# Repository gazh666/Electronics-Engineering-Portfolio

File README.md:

# Electronics Engineering Portfolio

**Power Electronics | Battery Management | Semiconductor Applications | PCB Design | Engineering Validation**

三个独立、可复现的电子工程项目：电池管理（BatteryLab）、电源电路仿真（PowerLab）、
自动化测试与工程验证（TestLab）。全部基于真实运行的 SPICE 求解、自动化测试与 KiCad EDA 检查，
不使用伪造数据、不把仿真写成实测、不隐藏失败结论。

> 本仓库为**个人工程研究原型**，未进行制板、焊接、上电或真实仪器/电池实验。
> 明确不含 **Production Ready / Hardware Validated** 表述。工程局限见
> [known_limitations.md](known_limitations.md)。

## 三个项目

- **BatteryLab — 电池管理系统**
  模拟前端采集、AFE 误差预算、MOSFET 保护、被动均衡、CC-CV 充电、SOC 估计，
  以及两套**真实可编辑的 KiCad 原理图 + 两块四层 PCB**。

- **PowerLab — 电源电路仿真**
  Buck 拓扑、功率器件非理想建模、效率与损耗分析、Pareto 多目标优化、PI 控制、软启动。

- **TestLab — 自动化测试与验证**
  SCPI 虚拟仪器、自动化测试、参数扫描、故障注入、工程验证与可靠性统计。

## BatteryLab 最终量化成果

每项均标注结果性质：`仿真` / `解析计算` / `公开数据分析` / `EDA 设计` / `软件测试`。

| 成果 | 数值 | 性质 | 证据 |
|---|---|---|---|
| 最坏情况电压采样误差预算 | 30.887 → 3.837 mV | 仿真 | `portfolio/BatteryLab_resume_metrics_v3.csv` |
| 最坏情况电流采样误差预算 | 37.736 → 6.666 mA | 仿真 | 同上 |
| 被动均衡单体压差 | 130 → 10.47 mV | 仿真 | 同上（B01） |
| 独立 MOSFET 保护 故障→电流抑制 | 0.871 µs | 仿真（SPICE 原始波形） | `BatteryLab/portfolio/BatteryLab_MOSFET保护真实性复验.md` |
| 联合系统保护 故障→电流抑制 | 119.8 µs（**RISK**） | 仿真 | `BatteryLab/portfolio/BatteryLab_研发岗成果证据卡_v3.md` |
| CC-CV 功率级效率 | 98.01 % | 仿真 | `BatteryLab/portfolio/BatteryLab_CC_CV控制优化前后对照.md` |
| CC 稳态误差 / CV 稳态误差 / CC→CV 过冲 | 1.09 mA / 13.50 mV / 2.07 mV | 仿真 | `BatteryLab/portfolio/BatteryLab_CC_CV控制优化前后对照.md` |
| SOC 估计 RMSE | 1.8247 个百分点 | 公开数据分析（CALCE 重放） | `BatteryLab/portfolio/BatteryLab_研发岗成果证据卡.md`（E01） |
| 可编辑原理图 | 2 套（BMS / 充电器） | EDA 设计 | `hardware/eda/*V2/` |
| 四层 PCB | 2 块，100.1 × 72.1 mm | EDA 设计 | `hardware/eda/*V2/release/routing_metrics.json` |
| 走线 / 过孔总数 | 620 段 / 96 个 | EDA 设计 | 两块板合计（304+316 / 46+50） |
| PCB 未连接项 | 65 / 51 → 0 / 0 | EDA 检查 | `release/unconnected_nets.csv` |
| DRC 错误 | 4 / 0 → 0 / 0 | EDA 检查 | `release/drc.json` |
| PCB 面积缩小 | 约 42 %（102×122 → 100.1×72.1 mm） | 解析计算 | [FINAL_DATA_AUDIT.md](docs/FINAL_DATA_AUDIT.md) |
| 软件回归测试 | 594 passed | 软件测试 | `BatteryLab/portfolio/BatteryLab_工程指标真实性核查报告_v3.md` |

> 以上均为仿真、解析计算、公开数据分析、EDA 设计或软件测试结果，
> **不是实际商业 BMS 板卡的硬件测量值**。

## PCB 真实预览（KiCad 导出 SVG）

以下为 `kicad-cli` 从实际 `.kicad_pcb` 导出的顶层/底层 SVG，不是渲染图或效果图。

**BMS V2（4 层，100.1 × 72.1 mm，304 段 / 46 过孔，0 未连接）**

**Charger V2（4 层，100.1 × 72.1 mm，316 段 / 50 过孔，0 未连接）**

**3D / STEP 查看说明**：本仓库**不提供伪造的 3D 渲染图**。如需 3D 视图，请下载
[BMS STEP](BatteryLab/hardware/eda/BatteryLab_BMS_V2/release/board.step) 或
[Charger STEP](BatteryLab/hardware/eda/BatteryLab_Charger_V2/release/board.step)，
用 KiCad PCB Editor、FreeCAD 或任意 STEP 查看器打开。

## 工程证据索引

- 完整证据索引：[docs/EVIDENCE_INDEX.md](docs/EVIDENCE_INDEX.md)
- 最终数据核查：[docs/FINAL_DATA_AUDIT.md](docs/FINAL_DATA_AUDIT.md)
- 前后工程对照：[BatteryLab/portfolio/BatteryLab_PCB工程设计前后对照.md](BatteryLab/portfolio/BatteryLab_PCB工程设计前后对照.md)
- ERC 告警分类：[BatteryLab/hardware/eda/review/schematic_warning_review.csv](BatteryLab/hardware/eda/review/schematic_warning_review.csv)
- 布线规划与叠层：[BatteryLab/hardware/eda/review/routing_plan.md](BatteryLab/hardware/eda/review/routing_plan.md)
- 性能优化前后对照：[BatteryLab/portfolio/BatteryLab_工程性能优化前后对照_v2.md](BatteryLab/portfolio/BatteryLab_工程性能优化前后对照_v2.md)
- 原理图 PDF：[BMS](BatteryLab/hardware/eda/BatteryLab_BMS_V2/release/schematic.pdf) /
  [Charger](BatteryLab/hardware/eda/BatteryLab_Charger_V2/release/schematic.pdf)

> 说明：原始运行输出（`results/`、pytest 日志）体积较大且含本机路径，**不随仓库分发**；
> 仓库内证据为汇总 CSV、验证文档与 EDA 发布文件，原始输出可按复现步骤在本地重新生成。

## 项目索引

| 项目 | 方向 | 关键技术 | 可复现证据 |
|---|---|---|---|
| [TestLab](TestLab/README.md) | 自动化测试 / 虚拟仪器 | PyVISA-sim、SCPI、行为模型 DUT、故障注入、可靠性、报告 | 557 passed、覆盖率 84%、发布验收 7/7 |
| [PowerLab](PowerLab/README.md) | 电源电路仿真 | PySpice 1.5 + ngspice 34、Buck 开环瞬态、CCM/DCM、理论对照 | ngspice 真实求解、11 项基础分析回归 |
| [BatteryLab](BatteryLab/README.md) | 电池采样 / 保护 / 充电 / EDA | 电池模型、AFE 误差预算、保护 SPICE、充电闭环、KiCad 4 层 PCB | 594 passed、ERC/DRC 0 错误、0 未连接 |

## 目录说明

```
Electronics-Engineering-Portfolio/
├── TestLab/                      # PyVISA-sim 自动化测试平台
├── PowerLab/                     # PySpice + ngspice 电源仿真
├── BatteryLab/                   # 电池软件链 + KiCad 硬件设计
│   ├── hardware/eda/
│   │   ├── BatteryLab_BMS_V1/    # 未布线工程草案（保留）
│   │   ├── BatteryLab_BMS_V2/    # 完成布线的工程研究版本
│   │   ├── BatteryLab_Charger_V1/
│   │   ├── BatteryLab_Charger_V2/
│   │   ├── requirements/         # 引脚映射、网络规则、接口定义
│   │   └── review/               # ERC 告警分类、QFN 审核、叠层、线宽计算
│   └── portfolio/                # 验收报告、前后对照、简历 v3/v4
├── docs/                         # 证据索引、复现步骤、许可与上传清单
└── known_limitations.md          # 已知工程局限（必读）
```

## 重要声明

1. **数据性质**：全部为 `spice_simulation` / `pyvisa-sim SCPI` / `behavioral_model` / EDA 检查结果，
   不是实验室实测。
2. **失败与风险照实保留**：保护联合工况 119.8 µs（RISK）、环路带宽分离 1.86×（FAIL）、
   负载阶跃超 300 mV 限值（FAIL/过载研究）、低 SOC 误差未达标（LIMITED）。
3. **EDA 边界**：PCB 已完成布线、DRC 0 错误 0 未连接，但热、EMI、阻抗、平面完整性、
   开关节点寄生参数均未验证，不得作为投产或实际电池接线依据。详见 [known_limitations.md](known_limitations.md)。
4. **许可证**：本人原创及 AI 辅助开发的代码采用 MIT；第三方代码、数据、SPICE 模型、封装及工具
   保留各自原始许可证，详见 [THIRD_PARTY_NOTICES.md](THIRD_PARTY_NOTICES.md)。
5. **AI 辅助**：代码整理与文档撰写使用了 AI 辅助；所有数值由仓库内脚本在本机计算，并保留原始输出。
6. **隐私**：仓库不包含密钥、令牌、账号、邮箱或个人绝对路径（上传前已做敏感信息扫描）。

## 复现

```powershell
# TestLab
conda create -n kaifa python=3.11 pip -y
conda run -n kaifa python -m pip install -r TestLab/requirements.txt -r TestLab/requirements-dev.txt
conda run -n kaifa python -m pytest TestLab/tests -q

# PowerLab（需要 ngspice DLL）
conda create -n kaifa_power python=3.11 pip -y
conda run -n kaifa_power python -m pip install -r PowerLab/requirements.txt
conda run -n kaifa_power pyspice-post-installation --install-ngspice-dll
conda run -n kaifa_power python -m pytest PowerLab/tests -q

# BatteryLab
conda create -n kaifa_battery python=3.11 pip -y
conda run -n kaifa_battery python -m pip install -r BatteryLab/requirements.txt
conda run -n kaifa_battery python -m pytest BatteryLab/tests -q
```

KiCad 部分需要 KiCad 10 与 `kicad-cli`，见 [BatteryLab/hardware/eda/review/tool_verification.md](BatteryLab/hardware/eda/review/tool_verification.md)。
完整复现步骤见 [docs/REPRODUCIBILITY.md](docs/REPRODUCIBILITY.md)。

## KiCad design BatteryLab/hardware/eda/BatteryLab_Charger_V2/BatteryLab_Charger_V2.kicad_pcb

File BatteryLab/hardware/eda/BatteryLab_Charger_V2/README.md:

# BatteryLab_Charger_V1 状态

**BLOCKED_NO_KICAD_GUI**：本机未安装 KiCad，本目录没有 KiCad 工程文件。
本阶段只完成了充电器**原理图级设计计算**，PCB 尚未开始。

已完成的输入：

- `../requirements/charger_design.yaml`：18 V→12.15 V/1 A、600 kHz、VFB=2.1 V
- `../requirements/charger_pin_mapping.csv`：25 行（24 引脚 + PAD）
- `../requirements/critical_net_rules.csv`：功率与采样网络规则
- `../component_selection/inductor_comparison.csv`：SRN6045-220M 选型
- `docs/84_bq24610_charger_design.md`：全部计算与依据

安装 KiCad 后的操作：

1. 新建工程并按引脚映射绘制原理图；
2. ERC 通过后再进入 PCB；
3. 已知待复核项：LC 谐振标称 11.07 kHz（低于 12–17 kHz）、30 V FET 对 32 V ACOV 的余量。

详见 `docs/78_kicad_environment.md` 与 `docs/90_stage8_final_validation.md`。

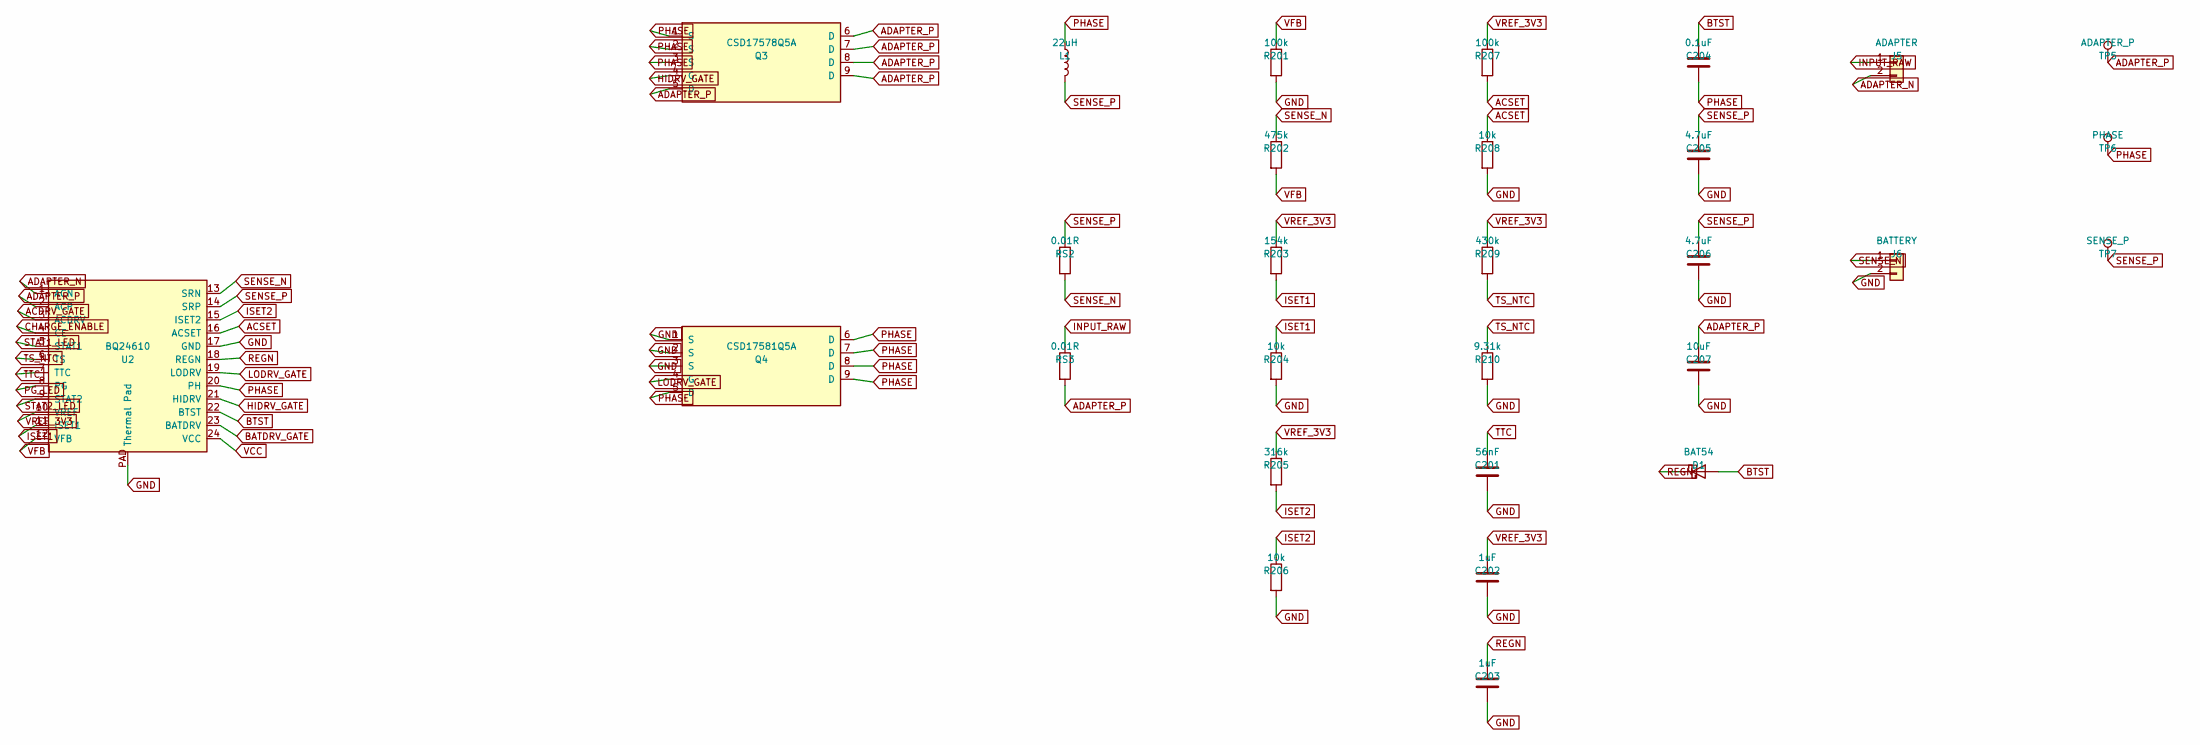
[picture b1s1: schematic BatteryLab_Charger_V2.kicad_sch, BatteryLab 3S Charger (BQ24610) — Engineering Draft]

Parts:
C201: 56nF; C_0603_1608Metric
C202, C203: 1uF; C_0603_1608Metric
C204: 0.1uF; C_0402_1005Metric
C205, C206: 4.7uF; C_1206_3216Metric
C207: 10uF; C_1206_3216Metric
D1: BAT54; D_SOD-323
J5: ADAPTER; PinHeader_1x02_P2.54mm_Vertical
J6: BATTERY; PinHeader_1x02_P2.54mm_Vertical
L1: 22uH; L_Bourns_SRN6045TA
Q3: CSD17578Q5A; Texas_S-PVSON-N8
Q4: CSD17581Q5A; Texas_S-PVSON-N8
R201, R207: 100k; R_0603_1608Metric
R202: 475k; R_0603_1608Metric
R203: 154k; R_0603_1608Metric
R204, R206, R208: 10k; R_0603_1608Metric
R205: 316k; R_0603_1608Metric
R209: 430k; R_0603_1608Metric
R210: 9.31k; R_0603_1608Metric
RS2, RS3: 0.01R; R_2010_5025Metric
TP5: ADAPTER_P; TestPoint_Pad_1.5x1.5mm
TP6: PHASE; TestPoint_Pad_1.5x1.5mm
TP7: SENSE_P; TestPoint_Pad_1.5x1.5mm
U2: BQ24610; Texas_RGE0024H_VQFN-24-1EP_4x4mm_P0.5mm_EP2.7x2.7mm

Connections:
ACDRV_GATE: U2.3 (ACDRV)
ACSET: R207.2, R208.1, U2.16 (ACSET)
ADAPTER_N: J5.2, U2.1 (ACN)
ADAPTER_P: C207.1, Q3.5 (D), Q3.6 (D), Q3.7 (D), Q3.8 (D), Q3.9 (D), RS3.2, TP5.1, U2.2 (ACP)
BATDRV_GATE: U2.23 (BATDRV)
BTST: C204.1, D1.2 (A), U2.22 (BTST)
CHARGE_ENABLE: U2.4 (CE)
GND: C201.2, C202.2, C203.2, C205.2, C206.2, C207.2, J6.2, Q4.1 (S), Q4.2 (S), Q4.3 (S), R201.2, R204.2, R206.2, R208.2, R210.2, U2.17 (GND), U2.PAD (Thermal Pad)
HIDRV_GATE: Q3.4 (G), U2.21 (HIDRV)
INPUT_RAW: J5.1, RS3.1
ISET1: R203.2, R204.1, U2.11 (ISET1)
ISET2: R205.2, R206.1, U2.15 (ISET2)
LODRV_GATE: Q4.4 (G), U2.19 (LODRV)
PG_LED: U2.8 (PG)
PHASE: C204.2, L1.1, Q3.1 (S), Q3.2 (S), Q3.3 (S), Q4.5 (D), Q4.6 (D), Q4.7 (D), Q4.8 (D), Q4.9 (D), TP6.1, U2.20 (PH)
REGN: C203.1, D1.1 (K), U2.18 (REGN)
SENSE_N: J6.1, R202.1, RS2.2, U2.13 (SRN)
SENSE_P: C205.1, C206.1, L1.2, RS2.1, TP7.1, U2.14 (SRP)
STAT1_LED: U2.5 (STAT1)
STAT2_LED: U2.9 (STAT2)
TS_NTC: R209.2, R210.1, U2.6 (TS)
TTC: C201.1, U2.7 (TTC)
VCC: U2.24 (VCC)
VFB: R201.1, R202.2, U2.12 (VFB)
VREF_3V3: C202.1, R203.1, R205.1, R207.1, R209.1, U2.10 (VREF)

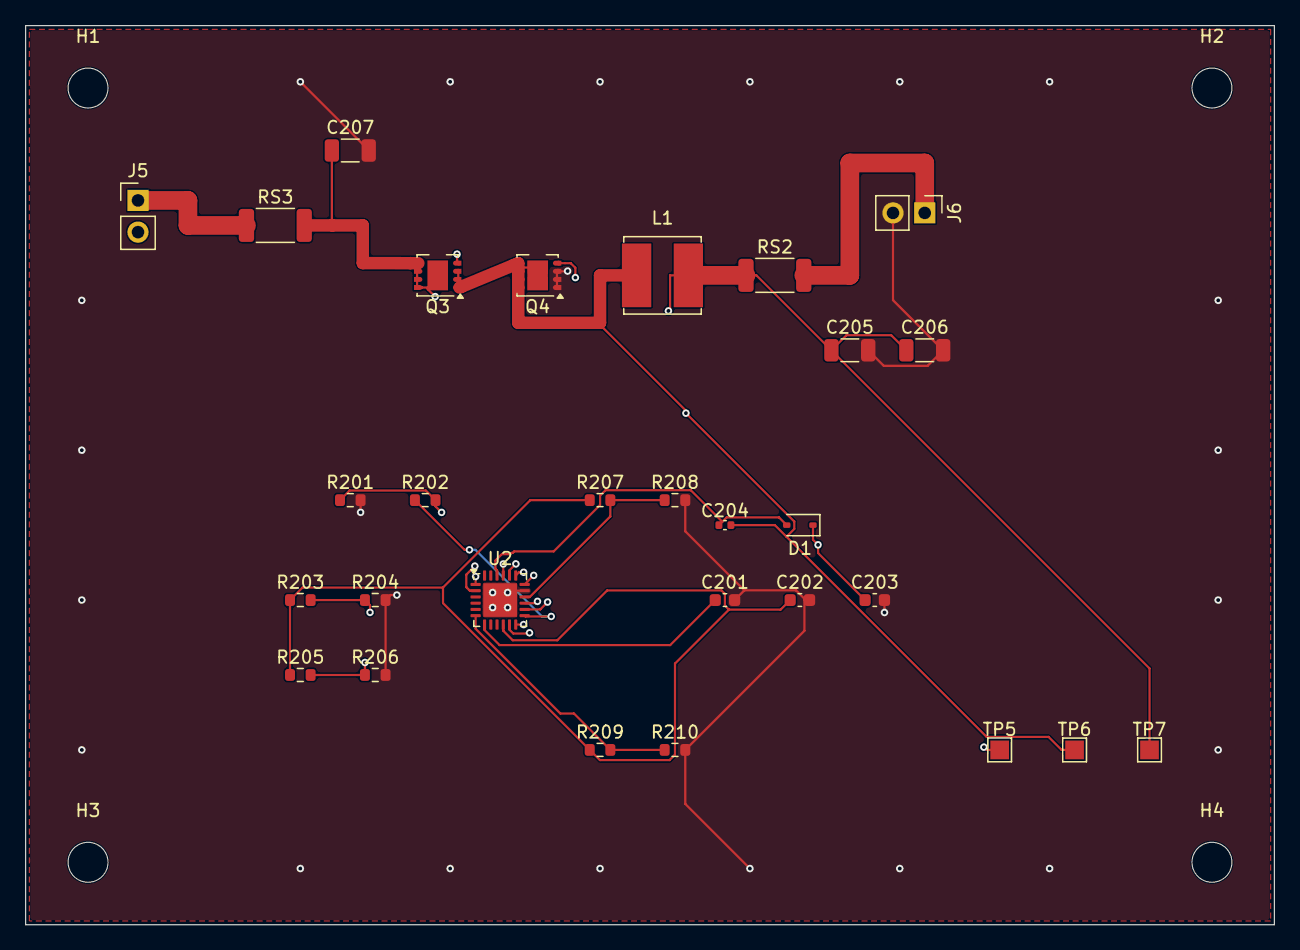
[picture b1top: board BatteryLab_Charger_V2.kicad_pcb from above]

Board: 4 copper layers, 100.0 x 72.0 mm, 33 parts (0 on the bottom side), 18 nets.

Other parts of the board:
H1, H2, H3, H4: MountingHole_3.2mm_M3

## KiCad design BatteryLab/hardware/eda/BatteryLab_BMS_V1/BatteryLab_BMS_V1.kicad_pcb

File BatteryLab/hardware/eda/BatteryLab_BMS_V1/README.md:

# BatteryLab_BMS_V1 状态

**BLOCKED_NO_KICAD_GUI**：本机未安装 KiCad，本目录没有 `.kicad_pro` /
`.kicad_sch` / `.kicad_pcb`。请不要把本目录当作已完成工程。

已完成的输入（可直接用于绘制原理图）：

- `../requirements/bms_design.yaml`：设计目标与 AFE 配置
- `../requirements/bms_pin_mapping.csv`：33 行（32 引脚 + PAD），逐行标注数据手册页码
- `../requirements/critical_net_rules.csv`：关键网络宽度/间距/层
- `../requirements/interface_definition.csv`：J1–J4、TP1–TP4
- `../../component_selection/`：器件与封装核查

安装 KiCad 后的操作：

1. 新建工程 `BatteryLab_BMS_V1.kicad_pro`；
2. 按引脚映射表放置符号并连线，封装按 `footprint_verification.csv` 核对；
3. 运行 `kicad-cli sch erc --format json ...`；
4. 布局布线后运行 `kicad-cli pcb drc --format json ...`；
5. 回到仓库根目录运行 `python -m scripts.audit_schematic` 与 `audit_pcb`。

详见 `docs/78_kicad_environment.md` 与 `docs/90_stage8_final_validation.md`。

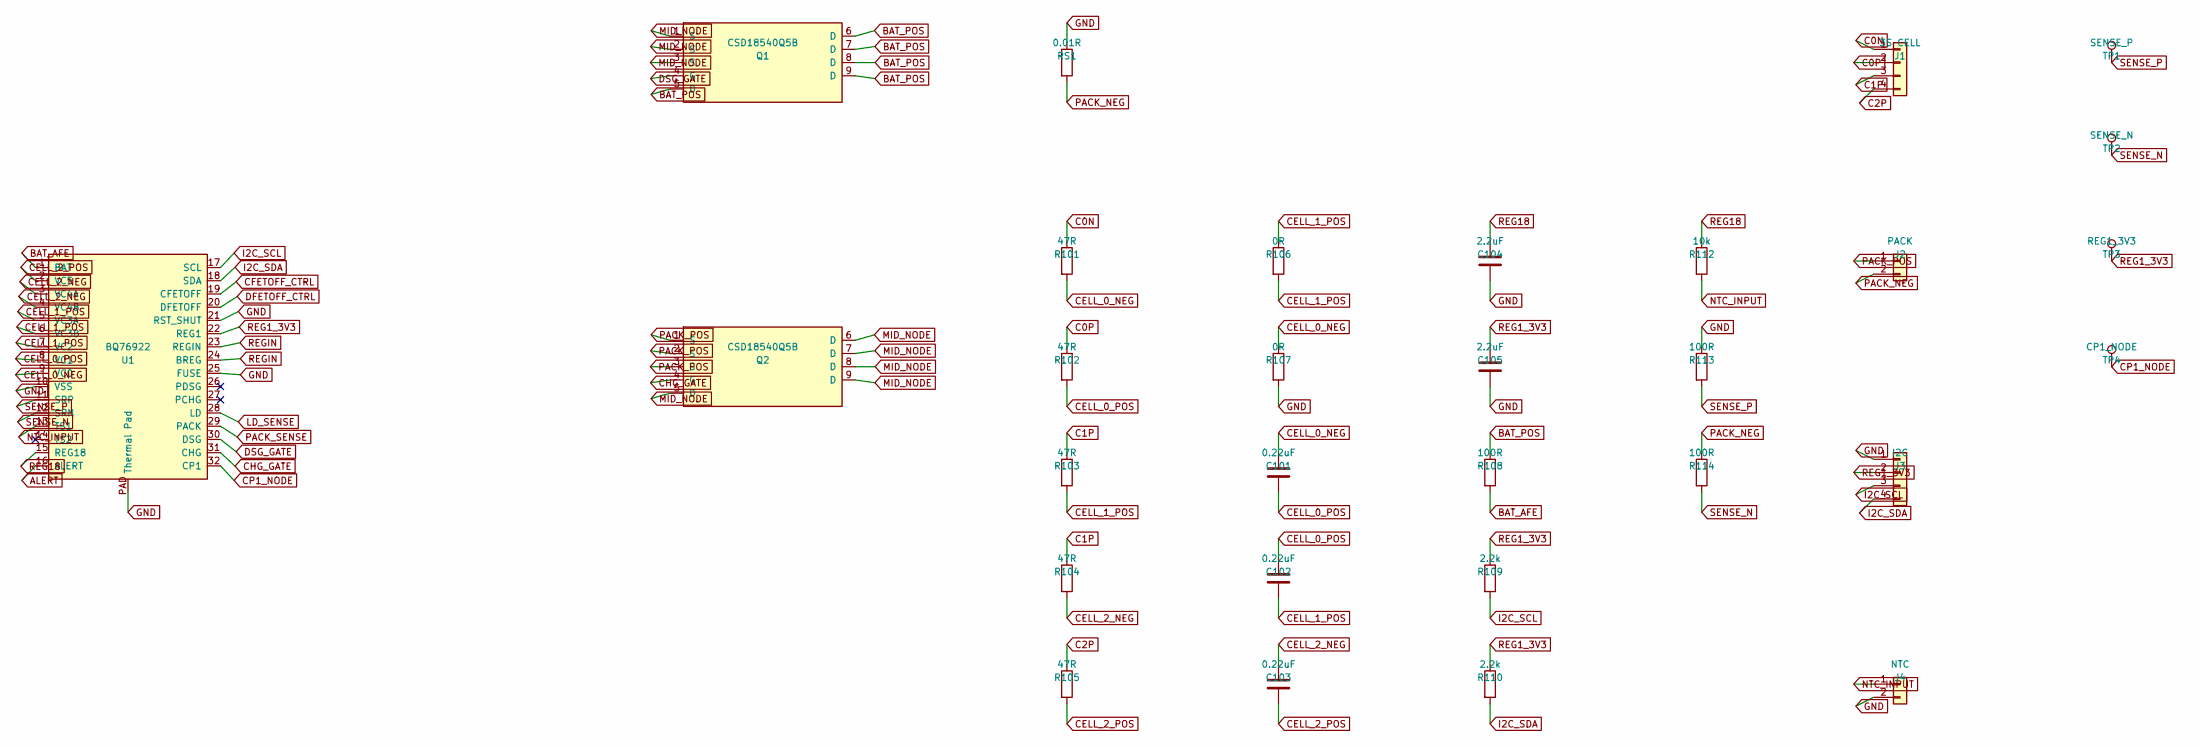
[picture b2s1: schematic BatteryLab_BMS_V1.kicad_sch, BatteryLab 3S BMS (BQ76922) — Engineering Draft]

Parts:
C101, C102, C103: 0.22uF; C_0402_1005Metric
C104, C105: 2.2uF; C_0603_1608Metric
J1: 3S CELL; PinHeader_1x04_P2.54mm_Vertical
J2: PACK; PinHeader_1x02_P2.54mm_Vertical
J3: I2C; PinHeader_1x04_P2.54mm_Vertical
J4: NTC; PinHeader_1x02_P2.54mm_Vertical
Q1, Q2: CSD18540Q5B; Texas_S-PVSON-N8
R101, R102, R103, R104, R105: 47R; R_1206_3216Metric
R106, R107: 0R; R_0603_1608Metric
R108, R113, R114: 100R; R_0603_1608Metric
R109, R110: 2.2k; R_0603_1608Metric
R112: 10k; R_0603_1608Metric
RS1: 0.01R; R_2010_5025Metric
TP1: SENSE_P; TestPoint_Pad_1.5x1.5mm
TP2: SENSE_N; TestPoint_Pad_1.5x1.5mm
TP3: REG1_3V3; TestPoint_Pad_1.5x1.5mm
TP4: CP1_NODE; TestPoint_Pad_1.5x1.5mm
U1: BQ76922; Texas_RSN_WQFN-32-1EP_4x4mm_P0.4mm_EP2.8x2.8mm

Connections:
ALERT: U1.16 (ALERT)
BAT_AFE: R108.2, U1.1 (BAT)
BAT_POS: Q1.5 (D), Q1.6 (D), Q1.7 (D), Q1.8 (D), Q1.9 (D), R108.1
C0N: J1.1, R101.1
C0P: J1.2, R102.1
C1P: J1.3, R103.1, R104.1
C2P: J1.4, R105.1
CELL_0_NEG: C101.1, R101.2, R107.1, U1.9 (VC0)
CELL_0_POS: C101.2, C102.1, R102.2, U1.8 (VC1)
CELL_1_POS: C102.2, R103.2, R106.1, R106.2, U1.5 (VC3A), U1.6 (VC3B), U1.7 (VC2)
CELL_2_NEG: C103.1, R104.2, U1.3 (VC4A), U1.4 (VC4B)
CELL_2_POS: C103.2, R105.2, U1.2 (VC5)
CFETOFF_CTRL: U1.19 (CFETOFF)
CHG_GATE: Q2.4 (G), U1.31 (CHG)
CP1_NODE: TP4.1, U1.32 (CP1)
DFETOFF_CTRL: U1.20 (DFETOFF)
DSG_GATE: Q1.4 (G), U1.30 (DSG)
GND: C104.2, C105.2, J3.1, J4.2, R107.2, R113.1, RS1.1, U1.10 (VSS), U1.21 (RST_SHUT), U1.25 (FUSE), U1.PAD (Thermal Pad)
I2C_SCL: J3.3, R109.2, U1.17 (SCL)
I2C_SDA: J3.4, R110.2, U1.18 (SDA)
LD_SENSE: U1.28 (LD)
MID_NODE: Q1.1 (S), Q1.2 (S), Q1.3 (S), Q2.5 (D), Q2.6 (D), Q2.7 (D), Q2.8 (D), Q2.9 (D)
NTC_INPUT: J4.1, R112.2, U1.13 (TS1)
PACK_NEG: J2.2, R114.1, RS1.2
PACK_POS: J2.1, Q2.1 (S), Q2.2 (S), Q2.3 (S)
PACK_SENSE: U1.29 (PACK)
REG1_3V3: C105.1, J3.2, R109.1, R110.1, TP3.1, U1.22 (REG1)
REG18: C104.1, R112.1, U1.15 (REG18)
REGIN: U1.23 (REGIN), U1.24 (BREG)
SENSE_N: R114.2, TP2.1, U1.12 (SRN)
SENSE_P: R113.2, TP1.1, U1.11 (SRP)

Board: 4 copper layers, 30 parts (0 on the bottom side), 26 nets, no tracks yet.
